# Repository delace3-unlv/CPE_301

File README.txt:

Welcome to my CPE 301 Repository

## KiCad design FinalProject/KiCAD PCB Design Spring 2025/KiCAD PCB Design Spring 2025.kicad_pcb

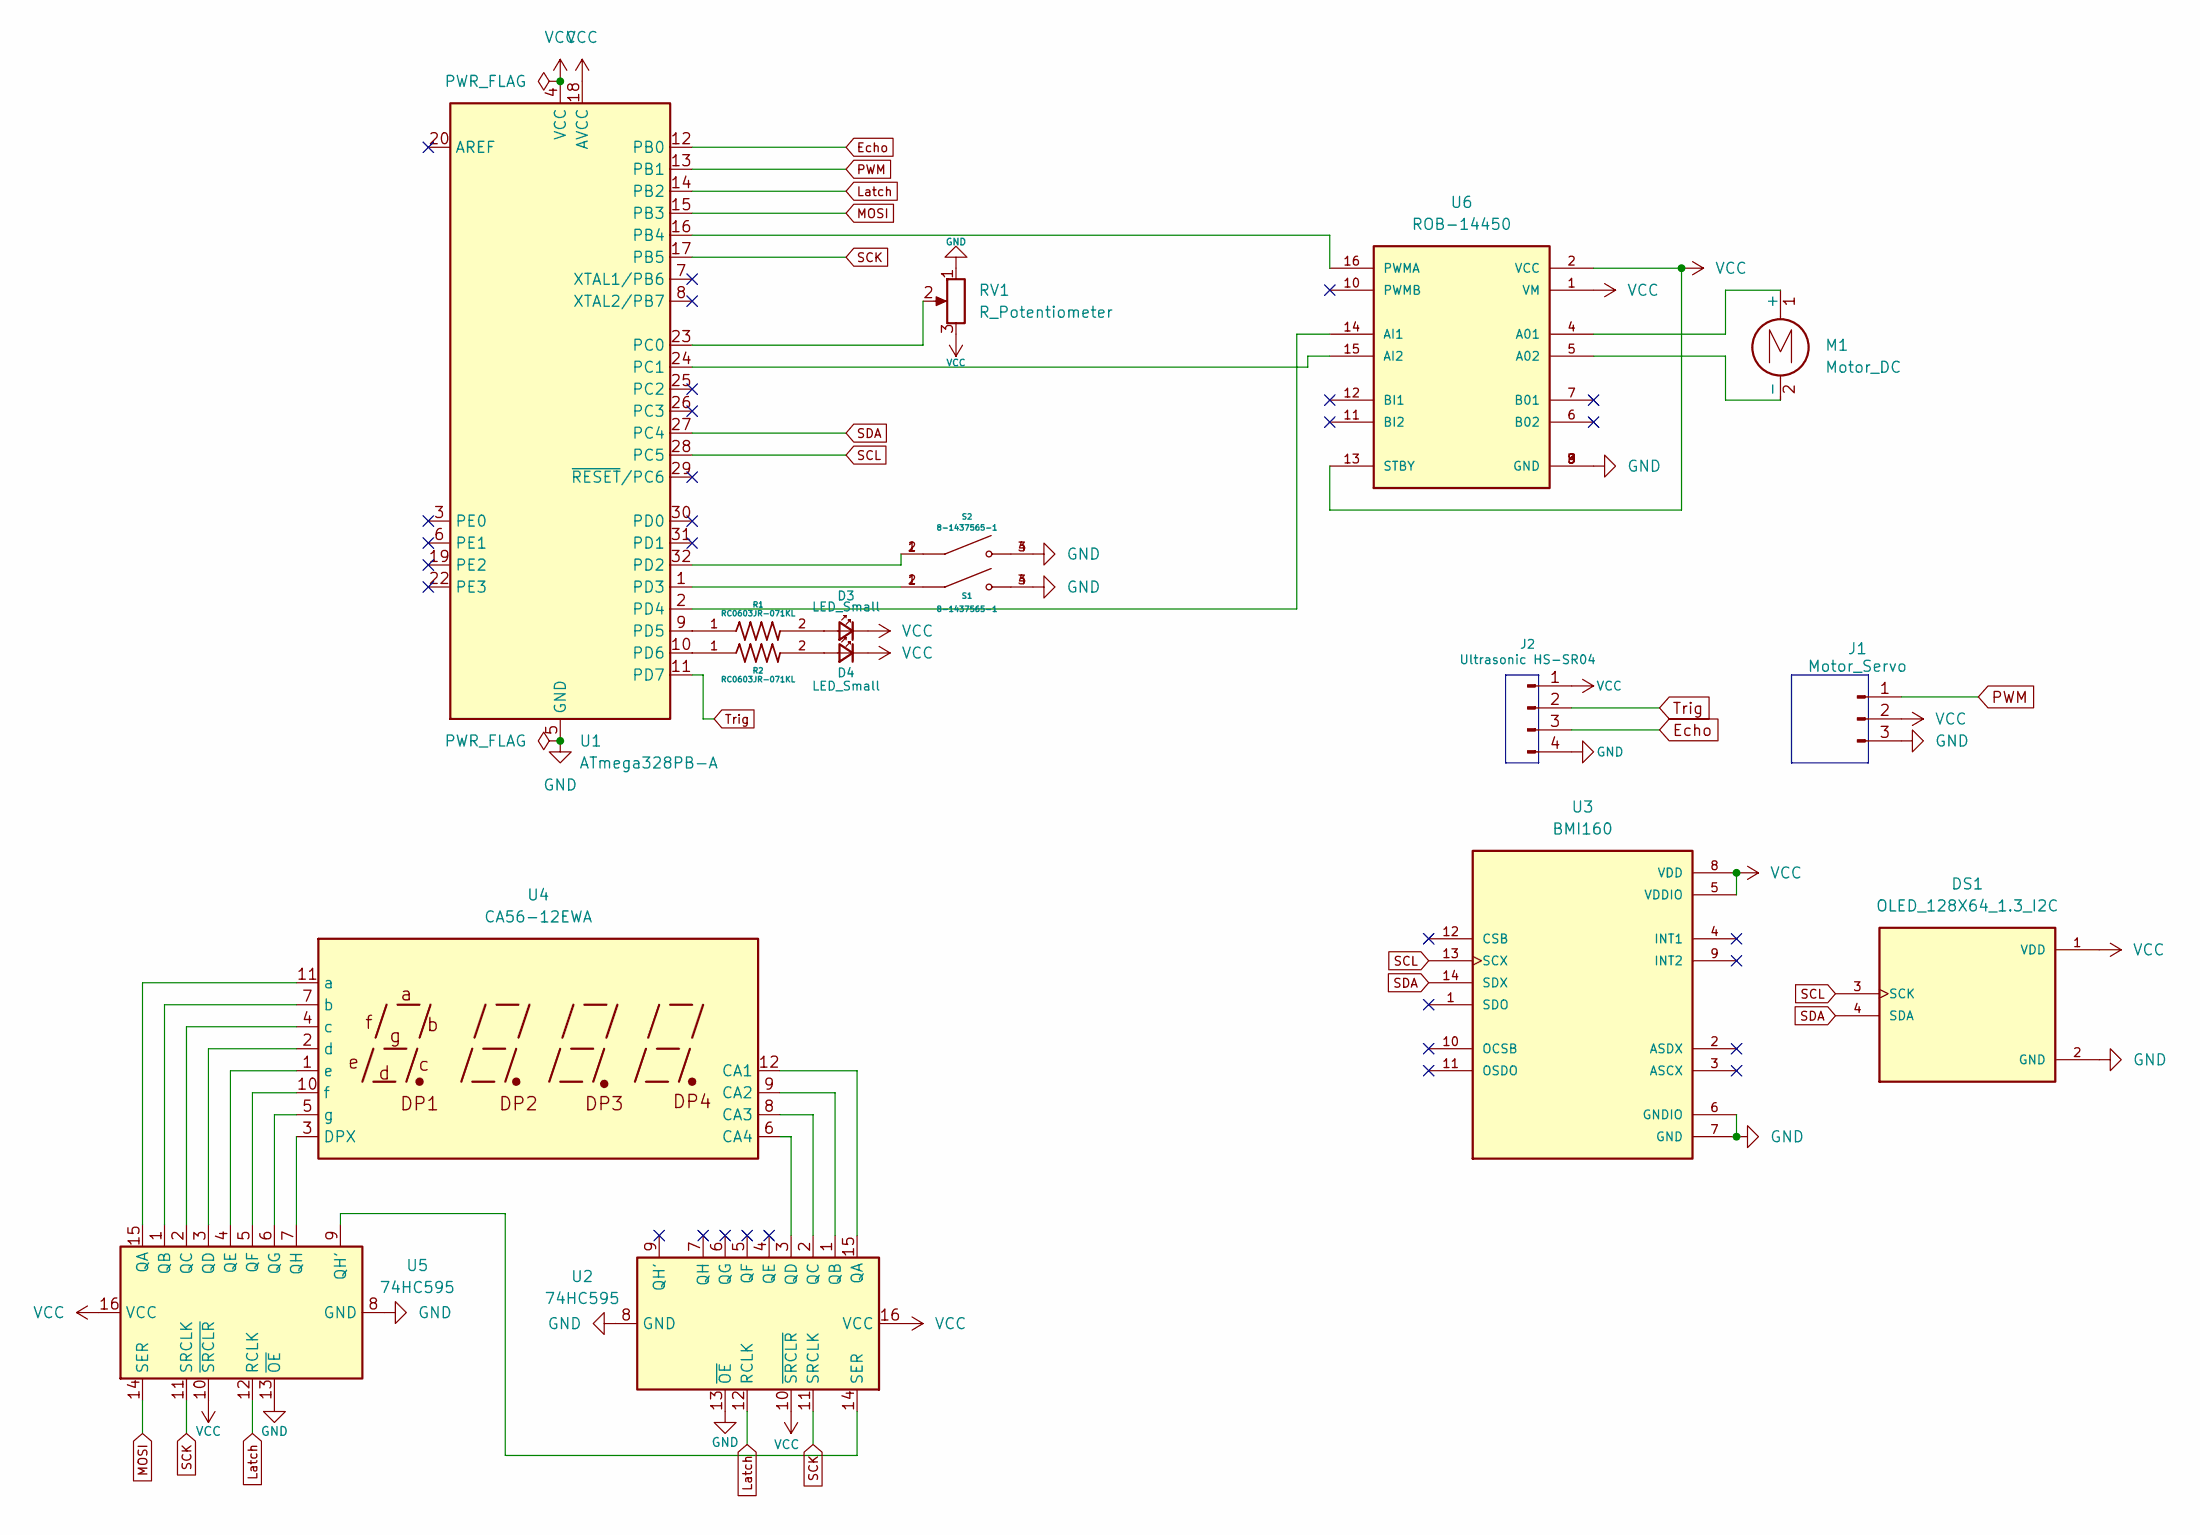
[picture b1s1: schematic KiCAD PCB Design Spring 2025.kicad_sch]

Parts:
D3, D4: LED_Small; D_SOD-123
DS1: OLED_128X64_1.3_I2C; LCD_OLED_128X64_1.3_I2C; PARTREV NA
J1: Motor_Servo; PinHeader_1x03_P2.54mm_Vertical
J2: Ultrasonic HS-SR04; PinHeader_1x04_P2.54mm_Vertical
M1: Motor_DC; PinHeader_1x02_P2.00mm_Vertical
R1, R2: RC0603JR-071KL; RESC1607X60N
RV1: R_Potentiometer; Potentiometer_ACP_CA9-V10_Vertical
S1, S2: 8-1437565-1; SW_8-1437565-1; PARTREV H3
U1: ATmega328PB-A; TQFP-32_7x7mm_P0.8mm
U2, U5: 74HC595; SSOP-16_5.3x6.2mm_P0.65mm
U3: BMI160; PQFN50P250X300X88-14N; PARTREV 1.0
U4: CA56-12EWA
U6: ROB-14450; MODULE_ROB-14450; PARTREV 11-13-17

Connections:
Echo: J2.3, U1.12 (PB0)
GND: DS1.2 (GND), J1.3, J2.4, RV1.1, S1.3, S1.4, S2.3, S2.4, U1.5 (GND), U1.21 (GND), U2.8 (GND), U2.13 (~OE), U3.6 (GNDIO), U3.7 (GND), U5.8 (GND), U5.13 (~OE), U6.3 (GND), U6.8 (GND), U6.9 (GND)
Latch: U1.14 (PB2), U2.12 (RCLK), U5.12 (RCLK)
MOSI: U1.15 (PB3), U5.14 (SER)
unnamed: D3.2 (A), R1.2
unnamed: D4.2 (A), R2.2
unnamed: M1.1 (+), U6.4 (A01)
unnamed: M1.2 (-), U6.5 (A02)
unnamed: U1.16 (PB4), U6.16 (PWMA)
unnamed: RV1.2, U1.23 (PC0)
unnamed: U1.24 (PC1), U6.15 (AI2)
unnamed: S2.1, S2.2, U1.32 (PD2)
unnamed: S1.1, S1.2, U1.1 (PD3)
unnamed: U1.2 (PD4), U6.14 (AI1)
unnamed: R1.1, U1.9 (PD5)
unnamed: R2.1, U1.10 (PD6)
unnamed: U2.15 (QA), U4.12 (CA1)
unnamed: U2.1 (QB), U4.9 (CA2)
unnamed: U2.2 (QC), U4.8 (CA3)
unnamed: U2.3 (QD), U4.6 (CA4)
unnamed: U2.14 (SER), U5.9 (QH')
unnamed: U4.3 (DPX), U5.7 (QH)
unnamed: U4.11 (a), U5.15 (QA)
unnamed: U4.7 (b), U5.1 (QB)
unnamed: U4.4 (c), U5.2 (QC)
unnamed: U4.2 (d), U5.3 (QD)
unnamed: U4.1 (e), U5.4 (QE)
unnamed: U4.10 (f), U5.5 (QF)
unnamed: U4.5 (g), U5.6 (QG)
PWM: J1.1, U1.13 (PB1)
SCK: U1.17 (PB5), U2.11 (SRCLK), U5.11 (SRCLK)
SCL: DS1.3 (SCK), U1.28 (PC5), U3.13 (SCX)
SDA: DS1.4 (SDA), U1.27 (PC4), U3.14 (SDX)
Trig: J2.2, U1.11 (PD7)
VCC: D3.1 (K), D4.1 (K), DS1.1 (VDD), J1.2, J2.1, RV1.3, U1.4 (VCC), U1.18 (AVCC), U2.10 (~SRCLR), U2.16 (VCC), U3.5 (VDDIO), U3.8 (VDD), U5.10 (~SRCLR), U5.16 (VCC), U6.1 (VM), U6.2 (VCC), U6.13 (STBY)

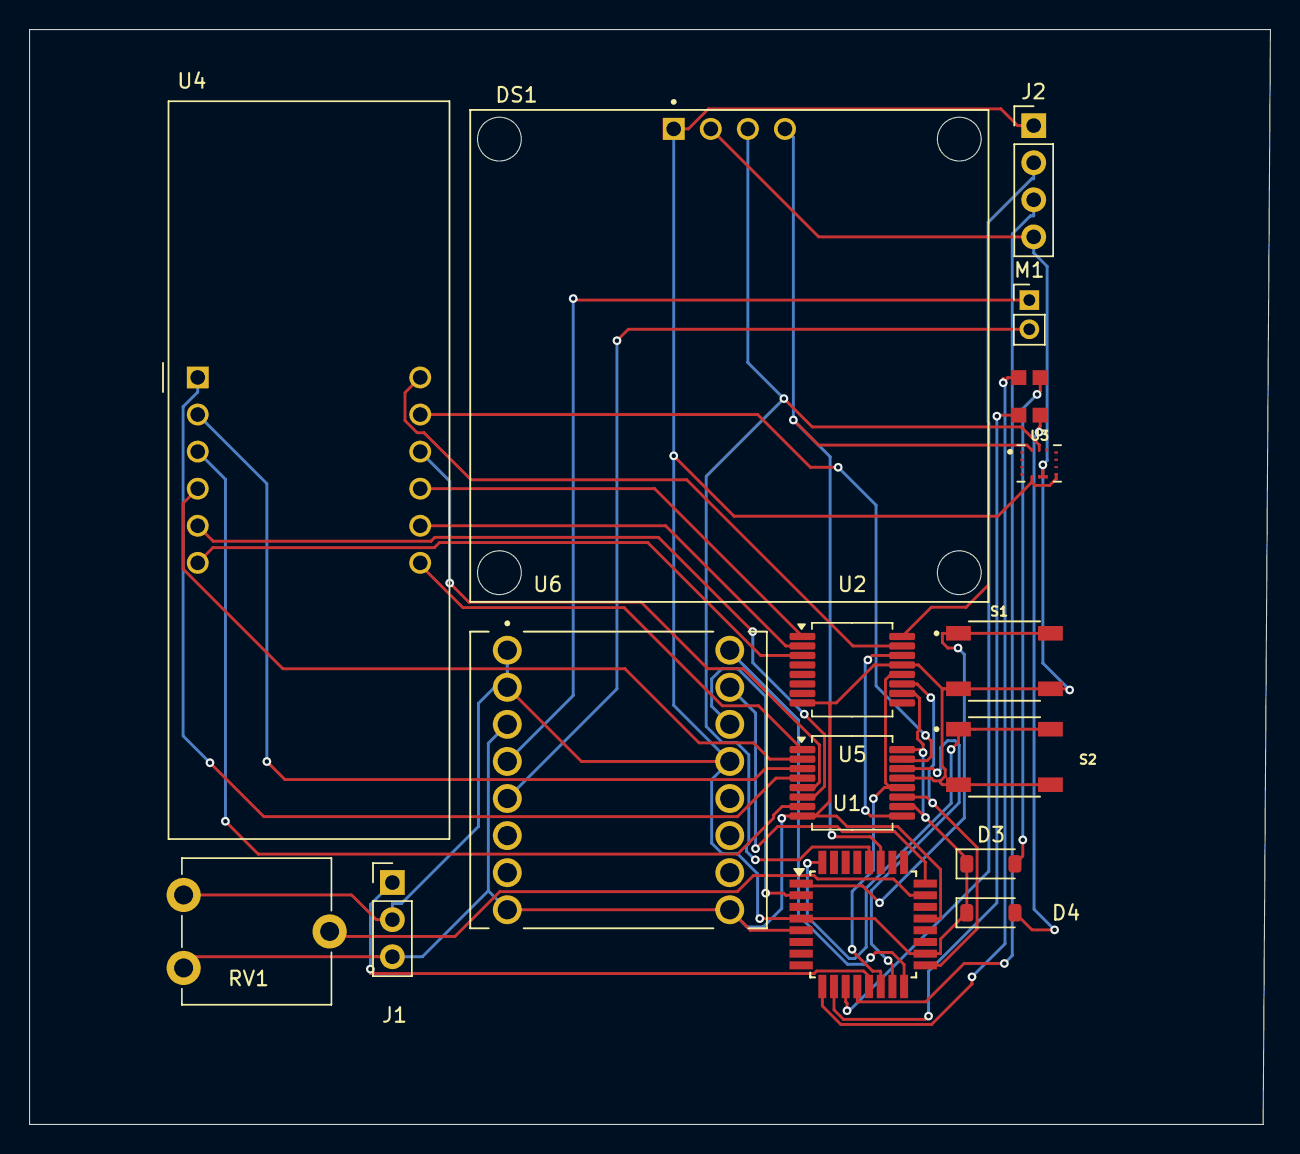
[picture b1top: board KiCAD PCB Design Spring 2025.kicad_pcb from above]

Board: 2 copper layers, 85.0 x 75.0 mm, 17 parts (0 on the bottom side), 35 nets.

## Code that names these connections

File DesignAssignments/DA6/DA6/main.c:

/*
 * DA6.c
 *
 * Created: 5/4/2025 4:48:00 PM
 * Author : enriq
 */ 

#define F_CPU 16000000UL
#include <avr/io.h>
#include <util/delay.h>
#include <avr/interrupt.h>
#include <stdio.h>
#include <stdint.h>

// 7-segment display
#define DATA      PB3
#define CLOCK     PB5
#define LATCH     PB2

// HC-SR04 | PB4 - TRIG | PB0 - ECHO
#define TRIG_DDR  DDRB
#define TRIG_PORT PORTB
#define TRIG_PIN  PB4

// Servo motor
#define SERVO_DDR   DDRD
#define SERVO_PIN   PD6      /* OC0A output */

static const uint8_t SEGMENT_MAP[10] = {
	0xC0,0xF9,0xA4,0xB0,
	0x99,0x92,0x82,0xF8,
	0x80,0x90
};
static const uint8_t SELECT_MAP[4] = {
	0xF1,0xF2,0xF4,0xF8
};
volatile uint8_t disp_digits[4];

static void shift_out_init(void) {
	DDRB |= (1<<DATA)|(1<<CLOCK)|(1<<LATCH);
	PORTB &= ~((1<<DATA)|(1<<CLOCK)|(1<<LATCH));
}

static void shift_out(uint8_t b) {
	for(uint8_t i=0;i<8;i++){
		if(b & (1<<(7-i))) PORTB |=  (1<<DATA);
		else               PORTB &= ~(1<<DATA);
		PORTB |=  (1<<CLOCK);
		PORTB &= ~(1<<CLOCK);
	}
}

ISR(TIMER2_OVF_vect) {
	static uint8_t idx=0;
	uint8_t seg=SEGMENT_MAP[disp_digits[idx]];
	uint8_t sel=SELECT_MAP[idx];
	PORTB &= ~(1<<LATCH);
	shift_out(seg);
	shift_out(sel);
	PORTB |=  (1<<LATCH);
	idx = (idx+1)&3;
}

static void tcnt2_init(void) {
	TCCR2A=0;
	TCCR2B=(1<<CS21)|(1<<CS20);
	TIMSK2=(1<<TOIE2);
}

static void display_number(int v) {
	disp_digits[0]=(v/1000)%10;
	disp_digits[1]=(v/100)%10;
	disp_digits[2]=(v/10)%10;
	disp_digits[3]=v%10;
}

// UART0 at 9600
static void uart_init(void) {
	UBRR0 = 103;  // 16MHz, 9600 baud
	UCSR0B = (1<<TXEN0);
	UCSR0C = (1<<UCSZ01)|(1<<UCSZ00);
}
static void uart_tx(char c) {
	while(!(UCSR0A&(1<<UDRE0)));
	UDR0=c;
}
static void uart_print(uint8_t angle, int mm)
{
	char buf[32];
	uint8_t n = snprintf(buf,sizeof(buf),
	"%u,%u\n", angle, mm);   // Angle, Distance in cm (I had it in mm before but cm is easier to read)
	for(uint8_t i=0;i<n;i++) uart_tx(buf[i]);
}

static int get_distance(void) {
	// reset timer
	TCNT1=0;
	TIFR1=(1<<ICF1);

	TRIG_PORT &= ~(1<<TRIG_PIN);
	_delay_ms(500);
	TRIG_PORT |=  (1<<TRIG_PIN);
	_delay_ms(500);
	TRIG_PORT &= ~(1<<TRIG_PIN);

	// rising edge
	TCCR1B |= (1<<ICES1);
	int t = 30000;
	while(!(TIFR1&(1<<ICF1)) && --t);
	if(!t) return 0xFFFF;
	int start = ICR1;

	// falling edge
	TIFR1 = (1<<ICF1);
	TCCR1B &= ~(1<<ICES1);
	t=30000;
	while(!(TIFR1&(1<<ICF1)) && --t);
	if(!t) return 0xFFFF;
	int end = ICR1;

	int us = (end - start) / 2;
	return ((us * 171UL) / 10000);
}

static void timer1_init(void) {
	TCCR1A=0;
	TCCR1B=(1<<CS11);
}

static void servo_init(void)
{
	SERVO_DDR |= (1<<SERVO_PIN);

	TCCR0A = (1<<COM0A1) | (1<<WGM00);
	TCCR0B = (1<<CS02)  | (1<<CS00);

	OCR0A  = 23;
}

static inline void servo_set_angle(uint8_t deg)
{
	if (deg > 180) deg = 180;
	OCR0A = 8 + ((int)deg * 8) / 180;
}

int main(void) {
	// disable ADC & comparator
	ADCSRA=0;
	ACSR  =(1<<ACD);
	DIDR0 =0x3F;

	// TRIG=output, ECHO=input
	TRIG_DDR |=  (1<<TRIG_PIN);
	DDRB     &= ~(1<<PB0);

	shift_out_init();
	tcnt2_init();
	uart_init();
	timer1_init();
	servo_init();
	sei();

	// clear display
	display_number(0);

	while(1) {
		static uint8_t  angle = 0;
		static int8_t   dir   = 1;       // +1 CW, -1 CCW

		servo_set_angle(angle);

		int distance = get_distance();
		uart_print(angle, distance);

		if (distance != 0xFFFF)			// update 7 seg only on a good echo
		display_number(distance);

		angle += dir * 6;
		if (angle >= 180) { angle = 180; dir = -1; }
		else if (angle == 0) { dir = 1; }

		_delay_ms(50);
	}
}

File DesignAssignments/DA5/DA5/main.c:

/*
 * DA5.c
 *
 * Created: 4/28/2025 10:44:50 PM
 * Author : enriq
 */ 

#define F_CPU 16000000UL
#include <avr/io.h>
#include <avr/interrupt.h>
#include <util/delay.h>
#include <stdlib.h>
#include <stdio.h>

// Motor driver pins 
#define IN1_PIN   PD4
#define IN2_PIN   PD5
#define PWM_PIN   PD6

// Variables
volatile uint16_t icr_last      = 0;
volatile uint16_t period_counts = 0;
volatile uint8_t  new_period    = 0;

uint8_t set_speed      = 0;  // 0255, PWM 
uint8_t measured_speed = 0;  // 0255, from measurement

// UART parsing 
char    rx_buf[4];
uint8_t rx_pos         = 0;
uint8_t override_flag  = 0;
uint8_t override_speed = 0;

// UART at 9600 baud 
static int uart_putchar(char c, FILE *stream) {
	while (!(UCSR0A & (1<<UDRE0)));
	UDR0 = (uint8_t)c;
	return 0;
}
static FILE uart_str = FDEV_SETUP_STREAM(uart_putchar, NULL, _FDEV_SETUP_WRITE);

void uart_init(void) {
	
	UBRR0  = F_CPU/16/9600 - 1;
	UCSR0B = (1<<TXEN0)|(1<<RXEN0);
	UCSR0C = (1<<UCSZ01)|(1<<UCSZ00);
	stdout  = &uart_str;
}

// ADC 
void adc_init(void) {
	ADMUX  = (1<<REFS0);                     
	ADCSRA = (1<<ADEN)|(1<<ADPS2)|(1<<ADPS1); 
}
uint16_t adc_read(void) {
	ADCSRA |= (1<<ADSC);
	while (ADCSRA & (1<<ADSC));
	return ADC;
}

// PWM (PD6)
void pwm0_init(void) {
	DDRD  |= (1<<PWM_PIN);
	TCCR0A = (1<<COM0A1)|(1<<WGM01)|(1<<WGM00); 
	TCCR0B =  (1<<CS01);                       
}

// ICP1 (PB0)
ISR(TIMER1_CAPT_vect) {
	uint16_t ic = ICR1;
	period_counts = ic - icr_last;
	icr_last      = ic;
	new_period    = 1;
}
void icap_init(void) {
	DDRB   &= ~(1<<PB0);                             
	TCCR1B  = (1<<ICNC1)|(1<<ICES1)|(1<<CS11);       
	TIMSK1  = (1<<ICIE1);                            
}

// Motor direction pins (PD4/PD5)
void motor_dir_init(void) {
	DDRD  |= (1<<IN1_PIN)|(1<<IN2_PIN);
	PORTD |=  (1<<IN1_PIN);  // IN1=1
	PORTD &= ~(1<<IN2_PIN);  // IN2=0 ? forward
}

int main(void) {
	motor_dir_init();
	pwm0_init();
	adc_init();
	uart_init();
	icap_init();
	sei();

	while (1) {
		
		if (UCSR0A & (1<<RXC0)) {
			char c = UDR0;
			if (c >= '0' && c <= '9' && rx_pos < sizeof(rx_buf) - 1) {
				rx_buf[rx_pos++] = c;
			}
			else if ((c=='\r' || c=='\n') && rx_pos) {
				rx_buf[rx_pos] = '\0';
				uint16_t v = atoi(rx_buf);
				if (v > 255) v = 255;
				override_speed = (uint8_t)v;
				override_flag  = 1;
				rx_pos = 0;
			}
		}

		// set_speed
		if (override_flag) {
			set_speed = override_speed;
			} else {
			uint16_t raw = adc_read();
			set_speed = raw >> 2;  
		}
		OCR0A = set_speed;

		// Update measured_speed 
		if (new_period) {
			new_period = 0;
			if (period_counts) {
				uint32_t freq = F_CPU/8/period_counts;
				measured_speed = (freq > 255 ? 255 : (uint8_t)freq);
				} else {
				measured_speed = 0;
			}
		}

		// Print on BAUD 9600
		uint16_t temp = ADC;  // last ADC reading
		printf("%u %u %u\n", temp, set_speed, measured_speed);


		_delay_ms(200);
	}
}

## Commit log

2025-02-24 Design Assignment 1: Assembly Programming - Memory Access
2025-02-24 setting up CPE 301 repo
2025-02-24 Assembly Programming - Memory Access
2025-03-23 re-organized everything and added DA2
2025-04-07 Design Assignment 4: ADC+UART
2025-05-13 kiCad final design
2025-05-14 KiCAD PCB Design Spring 2025
